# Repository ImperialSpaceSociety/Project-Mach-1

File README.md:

# Project-Mach-1
This repository contains information to support the high powered rocketry project at the Imperial College Space Society. It documents the electronic Command and Control Modules which are used within the project.

## Repository Structure
The repository structure is based on the high level electronics modules:

* [Flight Computer](https://github.com/ImperialSpaceSociety/Project-Mach-1/blob/master/Flight%20computer)
* [docs - Top Level Specfications and Documents](https://github.com/ImperialSpaceSociety/Project-Mach-1/blob/master/docs)

Each Module description has the following structure:

* ICSS Specifications
* External specifications, references and documentation
* Electronic Hardware (schematics and PCB)
* Firmware
* Physical Hardware (CAD)

## Quick Reference
The following is intended to provide a view for the casual browser of the project content.

* The [Flight Computer](https://github.com/ImperialSpaceSociety/Project-Mach-1/blob/master/Flight%20computer) has these key role:
  * Unambiguously capture flight data for subsequent analysis
  * Verify and prove performance record data ( Mach)
  * Support it's own successful recovery

## Rocket flight computer requirements:
* flexible for two stage or one stage rocket
* must have buzzer
* must have flashing LEDs to help with recovery on the ground
* must have usb programmer and possibly for accessing stored data
* 3 mosfets for rocket trigger, parachute triggering, spare
* rocket to ground telemetry link
* GPS for tracking and recovery
* runs at 3.3V logic levels(CMOS)
* 9 dof acclermoeter, gyroscope, compass. Max accleration would be 20g
* pressure(and temperature) sensor to measure altitude
* current sensing to see the amount of current going into fuses
* Mosfet must be able to supply 1.2 amps for at least 10milliseconds. Bridge wire resistance is 1.2-1.8 Ohms
* Must be able to run for at least 1 hour continueously
* must be hand solderable. Perferably
* 100Hz sample rate from sensors(except GPS)
* must record data continueously for at least 3min
* 14 parameters to record: *4 characters*:{accl_x, accl_y, accl_z, gyro_x, gyro_y, gyro_z, compass_x, compass_y, compass_z} + *6 characters:*{pressure}+ *3 characters:*{temperature}+ *7 characters*{Longitude, latitude}+*4 characters:*{altitude}
Assuming ascii encoding, 504 bits per string for raw data. Including commas and carriage return, each reading is ~600 bits.
* Total data storage required: 600bits * 60s * 100hz * 3min = 10.8 Mbits = 10800000 bits

## Major components of V1.1 flight computer
* ST Microelectronics H3LIS100DL: 100g 3-axis accelerometer
* ST Microelectronics LSM9DS1: 9 degree-of-freedom Accelerometer, Gyroscope and Magnetometer in 3 axis
* TE Connectivity MS5607: Temperature and pressure sensor
* Sillicon Labs SI4463: 433 Mhz ISM band Telemetry radio transceiver
* Ublox MAX M8Q: GPS module
* Atmel SAMD21J18: Microcontroller 64 pin TQFP package
* Vishay Si7232DN: Dual N-Channel 20 V (D-S) MOSFET for 2 channel pyros
* Molex 2066400001: GNSS Active Patch Antenna with Low-Noise Amplifier
* Winbond w25q64JV: Flash chip 64 Mbytes

# Flight history

This flight computer was launched in July 2021 but was not recovered. Its now very easy to program using platform.io. No need to mess with board files.

However, the flight computer has 4 major issues.
1. The telemetry radio is terrible. The max range is only around 80 meters, as we discovered at the launch site.
2. The flash chip is quite small. It can only record for around 40 minutes at 3-4 readings a second.
3. The flash write speed is slow. It could be a software issue. I could only write 3-4 readings a second.
4. The position of the power connector for battery is in an awkward position, making it difficult to attach the battery

It may be best to start from scratch using a well known processor, such as an ESP32, and a well designed radio module. From the flight, we discovered that the radio has to work flawlessly. Or else, we will loose the rocket. So maximising range and reliablity of the telemetery is vital. An off the shelf radio module as they will likely have all the RF systems optimised. Its quite hard to do it on a custom PCB.

## Software architecture
We use the Arduino development environment to program the rocket flight computer. We use the arduino board files based off the Adafruit ItsyBitsy M0 Express, which uses the G variant of the SAMD21. The flight computer uses the J variant. 

The main buses are as follows:

`wire` is the main I2C bus for the sensors including the:
* ST Microelectronics H3LIS100DL: 100g 3-axis accelerometer
* ST Microelectronics LSM9DS1: 9 degree-of-freedom Accelerometer, Gyroscope and Magnetometer in 3 axis
* TE Connectivity MS5607: Temperature and pressure sensor
* Ublox MAX M8Q: GPS module

`wire1` is connected to a grove connector on the PCB, but not currently connected to anything.

`Serial` is used for printing out debug info via USB to a serial monitor(running on a computer)

`Serial1` is used for a secondary connection to the Ublox MAX M8Q: GPS module

`SPI1` is used to connect the Winbond w25q64JV: Flash chip 64 Mbytes

`SPI` is used to connect to the Sillicon Labs SI4463: 433 Mhz ISM band Telemetry radio transceiver

## How to setup
# Burning the bootloader
1. Install Atmel studio. It can be downloaded from the [atmel site](https://www.microchip.com/mplab/avr-support/atmel-studio-7). Ensure that you download the SMART ARM MCU option like so: 
2. Connect up the flight computer to the J-Link EDU like so. Note the positions and colours of wires. Getting them the wrong way around could cause reverse polarity issues. The usb connector on the flight computer must be connected to the Computer.
3. Open up Atmel Studio and navigate to Tools > Device Programming like so: 
4. Ensure that the device selected is the ATSAMD21J18A. The default name may be a very similar looking name so make sure you don't mix it up. Click apply.: 
5. Now navigate to the `Memories` tab. You will now burn the custom Arduino boot loader into SAMD21 on the flight computer with Atmel Studio. The bootloader is found in the latest releases by adafruit: https://github.com/adafruit/uf2-samdx1/releases/. Look for the bootloader for the `itsybitsy_m0`. We can use the same bootloader as the Itsybitsy M0 from adafruit. Download the bootloader to your computer and select that file.

 Click the `Program` button once selected the right bootloader: 

Ideally, once the Arduino bootloader is uploaded, the Segger debugger will not be necessary anymore; All future programming can be done with the Arduino IDE.

# Using Platform.io to program the flight computer.
We use Platform.io to program the flight computer as its much more conventient than using the Arduino environment. The platform.ini file captures all the dependencies(libraries, board files) and automatically downloads them. It even downloads the complilers all in the background, so its a simple matter of a single click on the`upload` button to compile and upload to the flight computer.

### Project code
There are 4 pieces of code that are required.
1. [main_code](main_code/). This is the code that flies on the rocket flight computer. It polls all the sensors(GPS, Accelrometers, barometer) and logs them to the SPI flash chip 3-4 times a second. It runs FreeRTOS for scheduling. 
2. [ground_station_receiver](Software/Arduino%20code/ground_station_receiver/). This is the code that runs on the ground station. It will receive packets from the rocket flight computer, and print out the location of the flight computer(longitude, latitude, altitude) and the received signal strength.
3. [spi_flash_dumper](Software/Arduino%20code/spi_flash_dumper/). The flash dumper must be run on the flight computer after the launch. It will dump all the contents of the flash chip, which has stored all the flight data. The format will be in a csv format. The fields in each line will be in the following format:
```
gps_unix_time, gps_millisecond, timestamp, longitude, latitude, altitude, temperature, pressure, h3lis_gyro[0], h3lis_gyro[1], h3lis_gyro[2], h3lis_accelerometer[0], h3lis_accelerometer[1], h3lis_accelerometer[2], lsm9d_gyro[0], lsm9d_gyro[1], lsm9d_gyro[2], lsm9d_accel[0], lsm9d_accel[1], lsm9d_accel[2], lsm9d_mag[0], lsm9d_mag[1], lsm9d_mag[2]
```
4. [spi_flash_deleter](Software/Arduino%20code/spi_flash_deleter/). This program must be run to delete all the contents of the spi flash chip. After a flight, there is a good chance that the flash chip will be full, so delete all contents by running this code on there. Note, the user will have to type in `OK` into the serial terminal inorder for the erase to happen.

### How to upload to flight computer.
To get platform.io, install [Visual Studio code](https://code.visualstudio.com/). Then get the [platform.io](https://platformio.org/install) plugin. Then open the flight computer project you want to use. It should look like in the picture below. Hit the upload button as shown in the picture below to compile and upload to the flight computer. Also, ensure your computer in connected to the device via a USB cable. If all fails, try uploading the boot loader again as described in the [Burning the bootloader](#burning-the-bootloader) section.

# Using Arduino to program(depreciated)
This was the old way of programming the flight computer, but its no longer used. Use the method described in the [Using Platform.io to program the flight computer](#using-platformio-to-program-the-flight-computer) section.
1. Install the Arduino IDE
2. Install Arduino support for the SAMD series of microcontrollers. To do so, go to file > preferences and add `https://adafruit.github.io/arduino-board-index/package_adafruit_index.json` to Additional Board Manager Urls like so: 
3. Then go to Tools > Boards > Boards Manager like so:
4. Then install the SAMD core by searching for Arduino SAMD Boards (32-bits Arm Cortex-M0+) like so: 
5. Then install the Boards support for Adafruit SAMD boards, which our Flight computer is based off. Install version 1.5.9. Put in `Adafruit SAMD Boards` into the search bar.
6. Find out where your newly downloaded board files are found by going here to the file > preferences. In this case the board files are in `C:\Users\Medad\Documents\ArduinoData`. .
7. Now you will have to replace these board files with our own custom board files. Go to the directory found in the previous step and navigate to`ArduinoData\packages\adafruit\hardware\samd` where you will find a folder like `1.5.9`. Now you need to delete this folder, and replace it with our custom folder of board files that can be found in this repo: `Project-Mach-1\Flight computer\Software\Custom board files for flight computer\1.5.9`.
8. Now restart Arduino IDE so that it can update the board file location.
9. Now select the rocket flight computer as the board to use, like so in the picture: 
10. Now select the upload and serial port by going to Tools > Port:
11. Now run the i2c scanner program in `Project-Mach-1\Flight computer\Software\Arduino code\i2c_scanner` on the arduino editor. You will see data on the serial port like this: 

## How to run the main program.
Assuming you have completed the previous steps, navigate to `Project-Mach-1\Flight computer\Software\Arduino code\main_flight_computer_code` and run `main_flight_computer_code.ino` on the Arduino editor. This is where we will be doing further updates to the main project. Note how we directly add the library files into this project. These can be seen in the tabs at the top of the editor: 

The reason why we do this is the stock libraries downloaded directly from Arduino often have minor bugs which we have to fix. Therefore, we make a copy of the library files and load them directly into this project.

## libraries directory
All our libraries are kept here: `Project-Mach-1/tree/master/Flight%20computer/Software/Arduino%20code/libraries`

## IC information

## Diagnositics from the SI4463 chip we use
```
Get Device Info:

Revision: 11
Part: Si4463
Part Build: 0
Id: F
Customer: 0
ROM_ID: 3  (3 = revB1B, 6 = revC2A)
Rev External: 3
Rev Branch: 0
Rev Internal: F
Patch: 0
Func: 1
Radio Temperature: 27.88 deg C
Radio Voltage: 3.29 Volts
```

### Diagnostics of Flash chip
```
Initialising..........
Chip Diagnostics initiated.

No Chip size defined by user. Checking library support.
Chip identified. This chip is fully supported by the library.

SPIMemory Library version: 3.3.0

JEDEC ID: 0xEF7017
Man ID: 0xEF
Memory ID: 0x70
Capacity: 8388608
Max Pages: 32768
Unique ID: 114518745233664, 0x688C52A779213900
-----------------------------------------------------------------------------------------------------------------------------
							Testing library code
-----------------------------------------------------------------------------------------------------------------------------
			Function		Test result			     Runtime
-----------------------------------------------------------------------------------------------------------------------------
			Power Down		   PASS				      53 us
			Power Up		   PASS				      45 us

			Erase Chip		   PASS				      13.618 s
			Erase 72KB		   PASS				      214.66 ms
			Erase 64KB		   PASS				      163.17 ms
			Erase 32KB		   PASS				      119.84 ms
			Erase 4KB		   PASS				      39.14 ms
-----------------------------------------------------------------------------------------------------------------------------
			Data type		I/O Result	      Write time	      Read time
-----------------------------------------------------------------------------------------------------------------------------
			Byte			   PASS			108 us			48 us
			Char			   PASS			120 us			46 us
			Word			   PASS			124 us			48 us
			Short			   PASS			126 us			52 us
			ULong			   PASS			140 us			58 us
			Long			   PASS			128 us			52 us
			Float			   PASS			140 us			54 us
			Struct			   PASS			282 us			94 us
			Byte Array		   PASS			2.07 ms			458 us
			String			   PASS			408 us			164 us
-----------------------------------------------------------------------------------------------------------------------------

```

### Radio working
Image shows the view on SDR sharp when transmitting, and the RX data on a second flight computer. Transmissions done on the first one.

## Current progress
* 25/9/19: The circuit board design files have been sent for manufacturing. Renders are as shown below.

## TODO
* build a base station
* build the rocket
* write all driver code for rocket flight computer(consider using FreeRTOS)
* assemble all flight computer PCBs by soldering
* Test all functions
* Launch!

## License

Hardware is Licensed under CERN OHL v.1.2 or later https://www.ohwr.org/documents/294 No warranty is provided for this documentation implied or otherwise.

Software is licensed under MIT License.

MIT License

Copyright (c) 2018 Imperial College Space Society

Permission is hereby granted, free of charge, to any person obtaining a copy of this software and associated documentation files (the "Software"), to deal in the Software without restriction, including without limitation the rights to use, copy, modify, merge, publish, distribute, sublicense, and/or sell copies of the Software, and to permit persons to whom the Software is furnished to do so, subject to the following conditions:

The above copyright notice and this permission notice shall be included in all copies or substantial portions of the Software.

THE SOFTWARE IS PROVIDED "AS IS", WITHOUT WARRANTY OF ANY KIND, EXPRESS OR IMPLIED, INCLUDING BUT NOT LIMITED TO THE WARRANTIES OF MERCHANTABILITY, FITNESS FOR A PARTICULAR PURPOSE AND NONINFRINGEMENT. IN NO EVENT SHALL THE AUTHORS OR COPYRIGHT HOLDERS BE LIABLE FOR ANY CLAIM, DAMAGES OR OTHER LIABILITY, WHETHER IN AN ACTION OF CONTRACT, TORT OR OTHERWISE, ARISING FROM, OUT OF OR IN CONNECTION WITH THE SOFTWARE OR THE USE OR OTHER DEALINGS IN THE SOFTWARE.

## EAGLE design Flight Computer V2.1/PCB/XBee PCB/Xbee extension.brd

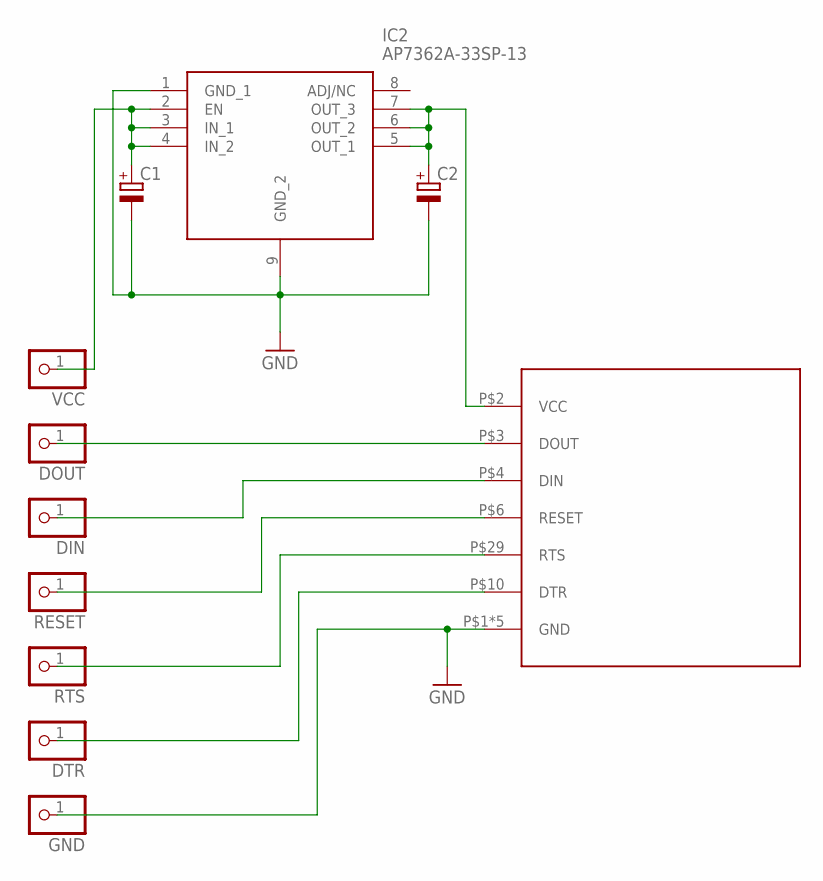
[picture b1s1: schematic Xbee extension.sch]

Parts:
C1, C2: CPOL-EU153CLV-0605; 153CLV-0605
DIN: PINHD-1X1; 1X01
DOUT: PINHD-1X1; 1X01
DTR: PINHD-1X1; 1X01
GND: PINHD-1X1; 1X01
IC2: AP7362A-33SP-13; SOIC127P600X150-9N
RESET: PINHD-1X1; 1X01
RTS: PINHD-1X1; 1X01
U$1: PRO_XTC
VCC: PINHD-1X1; 1X01

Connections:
GND: C1.-, C2.-, GND.1, IC2.1 (GND_1), IC2.9 (GND_2), U$1.P$1 (GND), U$1.P$11 (GND), U$1.P$13 (GND), U$1.P$22 (GND), U$1.P$35 (GND)
unnamed: C1.+, IC2.2 (EN), IC2.3 (IN_1), IC2.4 (IN_2), VCC.1
unnamed: DOUT.1, U$1.P$3 (DOUT)
unnamed: DIN.1, U$1.P$4 (DIN)
unnamed: RESET.1, U$1.P$6 (RESET)
unnamed: RTS.1, U$1.P$29 (RTS)
unnamed: DTR.1, U$1.P$10 (DTR)
unnamed: C2.+, IC2.5 (OUT_1), IC2.6 (OUT_2), IC2.7 (OUT_3), U$1.P$2 (VCC)

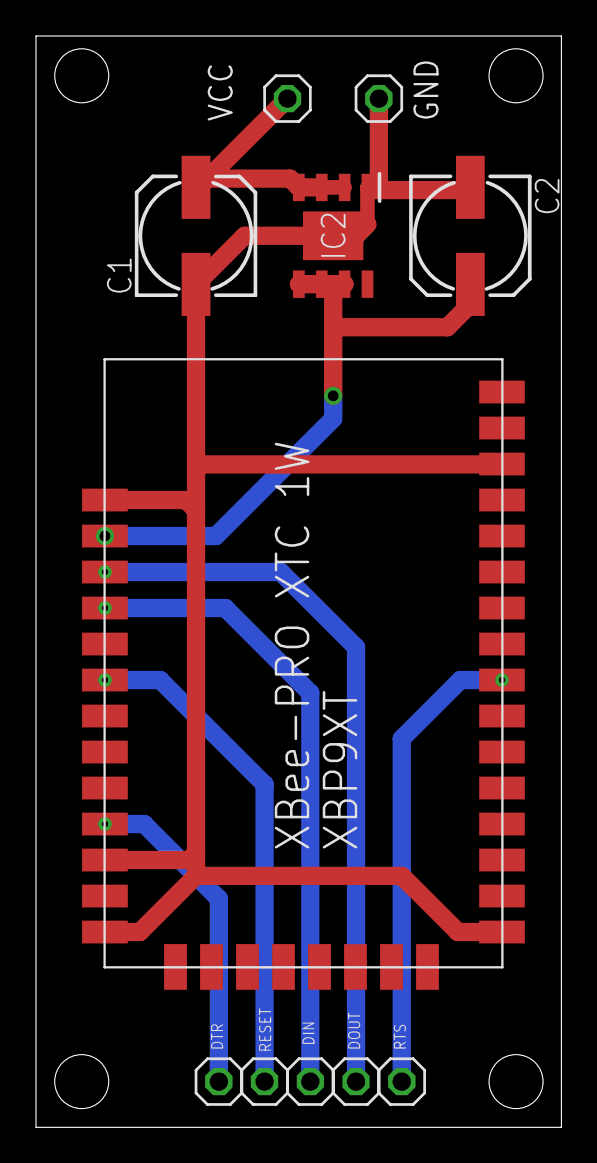
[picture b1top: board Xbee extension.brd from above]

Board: 2 copper layers, 29.2 x 60.6 mm, 11 parts (0 on the bottom side), 8 nets.

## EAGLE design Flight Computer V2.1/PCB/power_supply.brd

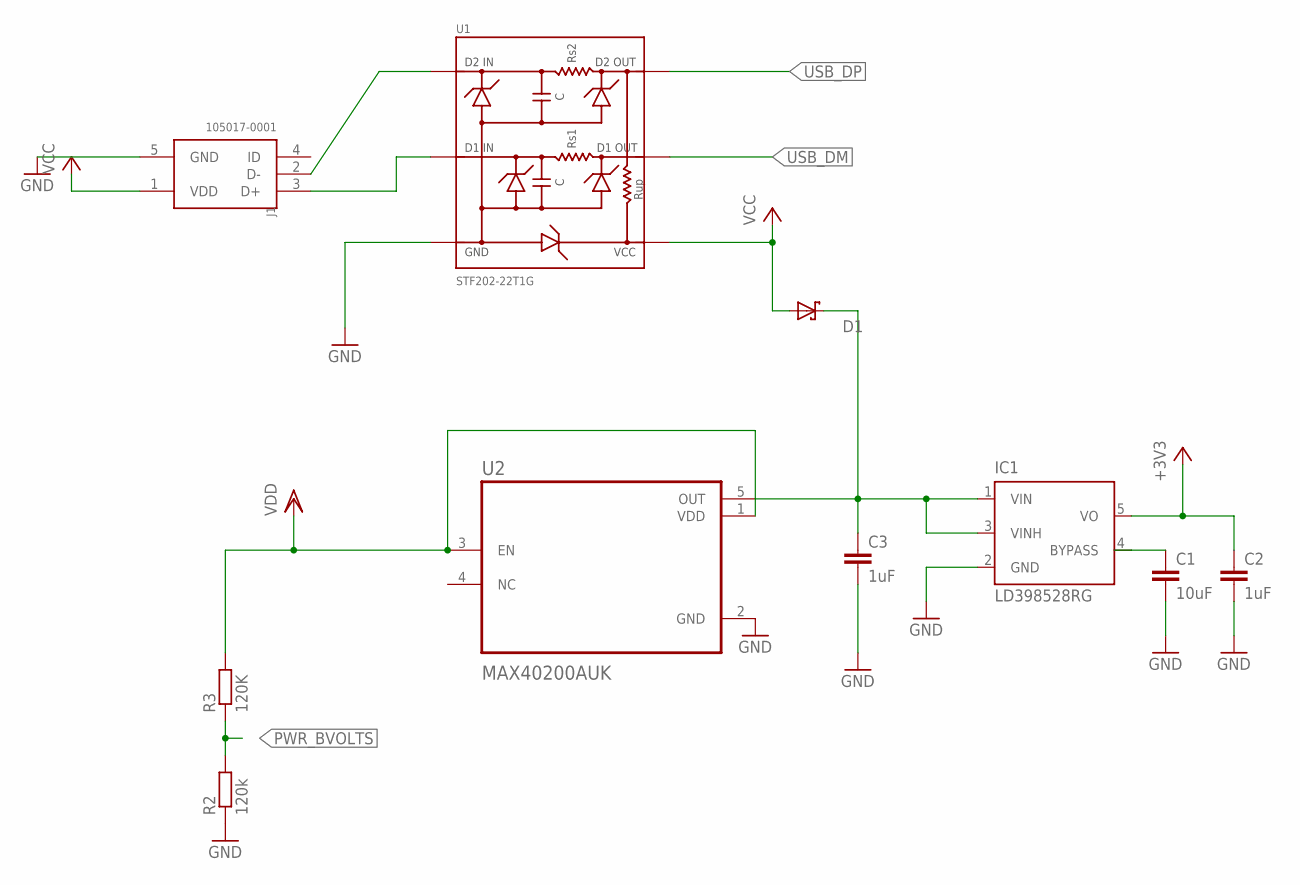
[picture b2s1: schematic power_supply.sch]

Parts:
C1: 10uF; C0603
C2, C3: 1uF; C0603
D1: SCHOTTKY-DIODEDFLS130L-7; POWERDI-123
IC1: LD398528RG; TSOT23-5L
J1: 105017-0001; MOLEX_105017-0001
R2: 120k; R0603
R3: 120K; R0603
U1: STF202-22T1G
U2: MAX40200AUK; 21-0057F

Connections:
+3V1: C3.1, D1.C, IC1.1 (VIN), IC1.3 (VINH), U2.5 (OUT)
+3V3: C2.1, IC1.5 (VO)
GND: C1.2, C2.2, C3.2, IC1.2 (GND), J1.5 (GND), R2.1, U1.6 (GND), U2.2 (GND)
unnamed: J1.2 (D-), U1.4 (D2-OUT)
unnamed: C1.1, IC1.4 (BYPASS)
PWR_BVOLTS: R2.2, R3.1
USB_DM: U1.2 (D1-IN)
USB_DP: J1.3 (D+), U1.3 (D2-IN), U1.5 (D1-OUT)
VCC: D1.A, J1.1 (VDD), U1.1 (VCC)
VDD: R3.2, U2.1 (VDD), U2.3 (EN)

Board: 2 copper layers, 10 parts (0 on the bottom side), 9 nets, no tracks yet.

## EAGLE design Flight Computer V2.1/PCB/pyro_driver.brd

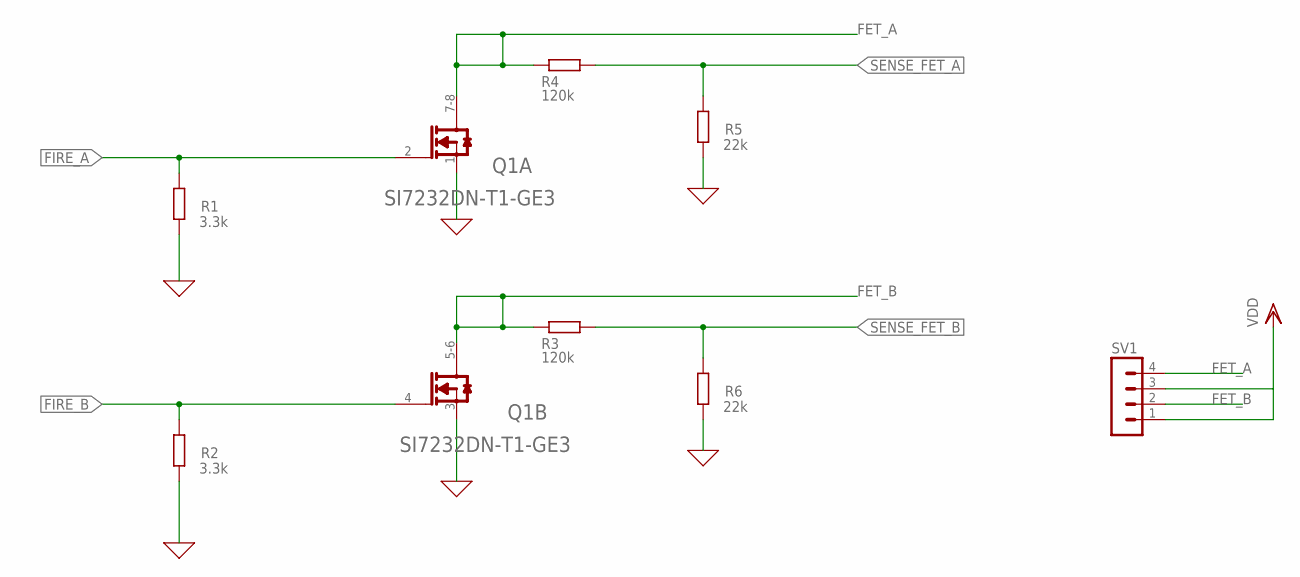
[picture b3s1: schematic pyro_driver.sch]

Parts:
Q1: VISHAY_SI7232DN-T1-GE3VISHAY_SI7232DN-T1-GE3_0_0; VISHAY_SI7232DN-T1-GE3_0
R1, R2: 3.3k; R0603
R3, R4: 120k; R0603
R5, R6: 22k; R0603
SV1: MA04-1

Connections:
0: Q1.1 (S1), Q1.3 (S2), R1.1, R2.1, R5.1, R6.1
FET_A: Q1.7-8 (D1), R4.1, SV1.4
FET_B: Q1.5-6 (D2), R3.1, SV1.2
FIRE_A: Q1.2 (G1), R1.2
FIRE_B: Q1.4 (G2), R2.2
SENSE_FET_A: R4.2, R5.2
SENSE_FET_B: R3.2, R6.2
VDD: SV1.1, SV1.3

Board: 2 copper layers, 8 parts (0 on the bottom side), 8 nets, no tracks yet.

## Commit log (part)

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2019-07-10 Update README.md
    Propose some structure for repository
2019-07-11 Create directory structure
2019-07-11 Link directories
2019-08-19 Simplified the structure
2019-08-19 added the right module names to readme
2019-08-19 added drawing of rocket
2019-08-23 Added documentation and also the references to all components
2019-08-24 Got the GPS wired up with the MAX-M8C.
    I wired up the MCU to the GPS as well. Sensors are also wired up to the I2C line.
    TODO:
    -make everything run on 3.3V
    - work out the pyro charges and drivers
    many more.
2019-08-24 Connected the SPI connection with the SIlabs radio and the XTAL
2019-08-31 Wired up the SI4463 according to AN628 figure 16. Component values have not been set. Only type of component.
2019-08-31 Swapped out the XTAL with a tcxo for radio.
2019-08-31 worked on the silabs 4463 radio chip
    - filled in the component values for TX matching and tx filtering
    - filled in tentative values for RX LNA matching. Will have to verify
    - swapped out XTAL and put in an RS Pro TCXO. Decoupled its powersupply.
2019-09-01 Change Tx Filter
2019-09-01 Radio Update
2019-09-02 added the library for the BMI088 to local directory
2019-09-02 changed all the paths for the schematic, footprints to local versions
    so that it will not break when others access from another computer
2019-09-02 changed the SPI flash chip
    -changed to Winbond W74M64FV 64Mbit flash chip to run on 3.3V. Changed schematic symbol and foot print.
    - changed the names of hierarchical labels for the pyros
2019-09-02 Wired the GYRO Ready and ACCL ready interrupt pins
2019-09-02 created net list for first time
    -changed SAML21 to J variant7
    -filled in foot prints for all components exept comparator
    -changed the footprints of ICSS pico tracker to a local copy
2019-09-04 more upgrades
    - removed the comparators
    - added the cost and link to buy components
    - added in a symbol for USB
2019-09-04 Wired up the FETs
    -fixed the ERC error for the BMI088 symbol
2019-09-04 connected 4 channels of pyro drivers
2019-09-04 put in the indicator LEDs
2019-09-04 removed the 37khz crystal
2019-09-04 swapped out the MCU from QFN to TQFP
    I suspect I will be making errors and almost certainly will have to jump wires. I think QFN is a nightmare to solder to.
2019-09-05 fixed errors with symbol and footprint connections
2019-09-05 added screw terminal symbols and anotated power supply page
2019-09-05 set up the PCB to fit formfactor
2019-09-05 Experimenting with arranging components on board. removed matching componets for GPS
2019-09-06 changed the footprint for 220 nH inductor and removed the circuit for low power voltage measurments
2019-09-06 removed the 100 ohm resistors on the gate of the pyro mosfets
2019-09-09 added in the foot prints for the 0433BM41A0019 integrated front end for SI4463
    U.FL_Hirose footprint and symbol added in for GPS active antenna
2019-09-09 added in the RF front end, exactly as stated in AN904
2019-09-09 put in a UFL connector in place of the Active GPS antenna
2019-09-09 added in some comments
2019-09-09 completed the pi circuit for Telemetry antenna
2019-09-09 changed the pin header to 2.54mm pitch for programmer and added a 3 pin header for antenna 434
2019-09-09 added pull down resistor to arm switch pin to prevent it from floating and accidentally fireing
2019-09-11 moved reset pin to programming pin header
2019-09-11 added in comment about where I got the ref layout for GPS+active antenna
2019-09-11 Added the USB protection IC
2019-09-12 added the arming switch. Changed foot print of lipo connector to JST
2019-09-12 updated the datasheet links and sites to purchase
2019-09-12 swapped out the 434 wire antenna for a Yageo434 chip antenna for smaller form factor
    I put in the 3D model for the te connectivity terminal blocks
2019-09-12 I put in a 4 terminal block for arming switch
2019-09-13 put in the Yageo 434 antenna
2019-09-13 Did Major reworking of ports
2019-09-13 added in the footprint for the 6 terminal block
    routed the RF section with the 434 antenna
2019-09-14 Done extensive routing of the board.
2019-09-15 only 2 or 3 connections left to route
2019-09-15 All connections routed!!
2019-09-16 Put in the Code for the flight computer and drivers.
2019-09-16 added in molex usb 3D cad and silk screen ICSS logo
2019-09-16 added links for purchasing some of the parts
2019-09-16 Precisely aligned the mounting holes
2019-09-16 done for today
2019-09-17 added in crystal footprint
2019-09-17 Finished routing the board with 3.3V power plane
    Power for mosfets comes from 2mm tracks on top layer. Todo: make their connection to ground more robust
2019-09-17 updated some of the purchase links
2019-09-17 added in copper pour to top and bottom layer. Change SPI flash chip
2019-09-18 forced to commit
2019-09-18 test
2019-09-18 remove merging conflicts
2019-09-18 changed SPI flash chip
2019-09-18 Flood fill top and bottom layer
2019-09-18 added in excel bill of material. Swapped out SAML for SAMD. They are pin compatible
2019-09-22 made a new folder for flight computer v1.1 for the 38mm size minimum diameter rockets
2019-09-23 put in new acclerometers and 9dof sensor. Changed supplier from mouser to farnell and RS
2019-09-23 Fully routed board v1.1 with the new high g accelerometer
2019-09-23 flood fill top and bottom layers
2019-09-24 put in logo for V1.1
2019-09-24 changed GPS to M8Q and included the diode from V bus to foot print which I missed out
2019-09-24 added in grove connector for break out pins. Made a new software framework for SAMD
2019-09-24 added 3d model of grove connnector
2019-09-25 sent for pcb manufacturing
2019-09-27 added in renders of the flight computer
2019-10-01 updated links to purchase
2019-10-11 put in the last bom purchase links
2019-11-07 put in blink software
2019-11-08 put in code
2020-01-21 added in arduino code and board files
2020-01-22 added in variants for rocket flight computer
2020-01-23 put in some working arduino c files. updated variant.cpp and variant.h.
    I2C and GPS still not working
2020-02-06 Got i2c working with changes to variant.cpp and variant.h
2020-02-13 removed unecessary board files
2020-02-18 Put in main flight computer code folder
2020-02-18 put in code for the h3Lis100 into main
2020-02-20 made main code work
2020-02-20 changed spi pin adresses and pads on the bottom of file
2020-02-20 9-degree acc added
2020-02-20 corrected PAD_SPI_TX and PAD_SPI_RX to the correct ones
2020-02-21 added in flash diagonostics with correct chip select pin defined
2020-02-26 First comit on new branch
    Changed variant files to be more specific to flight computer. Less general purpose Arduino and focuseed on actual hardware. Checked both USb and GPS serial and both wire interfaces.
    ** Note pin numbers have changed**
2020-02-27 Fixed SPI definitions in Variant.h
    Corrected conflicting and multiple definitions for SPI in varaint.c. Not tested though
2020-10-23 move all atmel studio projects into single folder
2020-10-23 put in dependency libraries for adafruit libraries
2020-10-27 put in printout of info in main program
2020-10-27 update flash chip in BOM
2020-10-27 updated ports info
2020-11-10 fixed the computer pin
2020-11-10 Implement a function to sample the GPS/GNSS sensor
2020-11-10 Remove unnecessary ==
2020-11-10 removed uncessary import of SPI
2020-12-01 Added blinking lights when landed
2020-12-01 adding the data packets, read and print functions
2021-02-09 adding write functionality to flash memory, writes contiguous stream to memory
2021-02-16 added stop after n seconds functionality, test results before run, and erase chip option
2021-02-16 radio send commands
    fixed sending of gps data in one pulse and added a simple send commands through terminal
2021-02-16 use neater declaration
2021-02-16 fix bug with referencing pointer
2021-02-16 Send Radio transmission every 10ms
2021-02-16 update comment
2021-02-16 send data only if gnd station mode
2021-02-16 remove duplicated library files
    It is already in the directory of the main_flight_computer_code
2021-02-16 return import back to original method
2021-02-16 put instructions for installing the library files for radio
2021-02-23 Put in rocket flight computer modes documentation
2021-02-25 Update variant.cpp
    Corrected pin mapping and ADC channels, all three ADC pins work.
2021-02-25 Battery level reading
    Created a function reading the voltage level, it also calculates percentage of the battery given min and max voltages
2021-06-17 make blink agnostic of the correct board files
2021-06-17 put in platform io and blinky
2021-06-17 switch to the J variant
2021-06-17 set correct variant
2021-06-17 put in variant files for the rocket flight computer board.
    Platform io will look for this custom files. Importantly, it tracks the variants in version control, and is sharable.
2021-06-18 move variants files into the boards folder
2021-06-18 add library dependencies
2021-06-18 put in main code
2021-06-18 auto format
2021-06-18 format and import
2021-06-18 adapt to multi file
2021-06-18 compiles
2021-06-18 make it compile the gps tasks as well
2021-06-18 reorganise repo to reduce file name length
    Windows complains that the filename lengths become too long
2021-06-18 Send message to ublox only after initialising.
2021-06-18 organise
2021-06-18 organise better
2021-06-18 use standarised naming
2021-06-18 print format
2021-06-18 put in rtos version
2021-06-18 move user commands to another file
2021-06-18 run diagnositcs first
2021-06-19 use channel 0
2021-06-19 set packet size to 64 bytes
2021-06-21 put in A repeated at 8 times speed
2021-06-21 use #define for our char
2021-06-21 sends out "f" ascii, as intended sometimes
2021-06-21 put big b
2021-06-21 run high speed f
2021-06-21 simplified f
2021-06-21 add in buzzer
2021-06-21 downgrade spi memory lib to v3.3
    fixes #16
2021-06-21 switch to using github package
2021-06-21 update to repo with right i2c address
2021-06-22 create sdfat_format
2021-06-22 fixed issue with rubbish data from ms5607
    fixes #19
2021-06-22 specify the silabs pins for our board
    fixes #20
2021-06-23 use file system
2021-06-23 put in examples of file system
2021-06-23 don't do full test run
2021-06-24 remove old flash functions
2021-06-24 adapt file system files
2021-06-24 increase sensor thread memory
2021-06-24 use our file inplementation
2021-06-24 remove spi memory
2021-06-24 use pointer to file
2021-06-24 use long form method for saving to flash
2021-06-25 add in working 2 way comms
2021-06-25 send data over radio
2021-06-25 temporarily disable flash and sensors
2021-06-25 allow sensor read
2021-06-25 printout out percentage and voltage
2021-06-25 move code folder to make filepaths shorter
2021-06-25 shorter name for folder
2021-06-25 revert back to using default libraries
    Or the device hangs.
2021-06-25 remove all flash code
2021-06-25 put in flash code
2021-06-25 log custom datastruct
2021-06-26 use adafruit spiflash for datastorage
2021-06-26 don't put into RX mode
    because the program in the library uses delay microseconds to wait for RX. Holds up every other thread when using delay microseconds
2021-06-26 no whiles
2021-06-26 save datapacket
2021-06-26 use vtaskdelay
    Immediately, processor utilisation falls from 50% to 1%
2021-06-26 print debug
2021-06-26 log timestamp
2021-06-26 access datapacket from outside
2021-06-26 fix bug in sending
2021-06-26 make more readable
2021-06-26 lat before long
2021-06-26 make datapacket more efficient
2021-06-26 flush instead of close
2021-06-26 sample every 50 ms
2021-06-26 goldilocks priorities
2021-06-26 dont use delay
2021-10-04 put in flash dumper
2021-10-04 put in flash chip deleter
2021-11-19 Created text files for ideas
    Put your ideas in relevant text files
2021-11-19 new sensors added
2021-11-26 pyro_driver
2021-11-27 Moved to proper folder
2021-12-02 added radio links
2021-12-03 Update and rename Radio ideas.txt to Radio ideas.md
    Added SX1278 and RFM95 radios
2021-12-06 eagle_power_supply
2021-12-09 Added component
2021-12-09 Pressure sensor additions
2022-01-15 Added sensors schematic and updated pyro_driver schematic
    Added the external libraries used for the components as well. Everything is saved under Project-Mach-1\Hardware\circuit board design v1.1\Eagle versions
2022-02-04 Added sensor schematic and updated pyro driver schematic
